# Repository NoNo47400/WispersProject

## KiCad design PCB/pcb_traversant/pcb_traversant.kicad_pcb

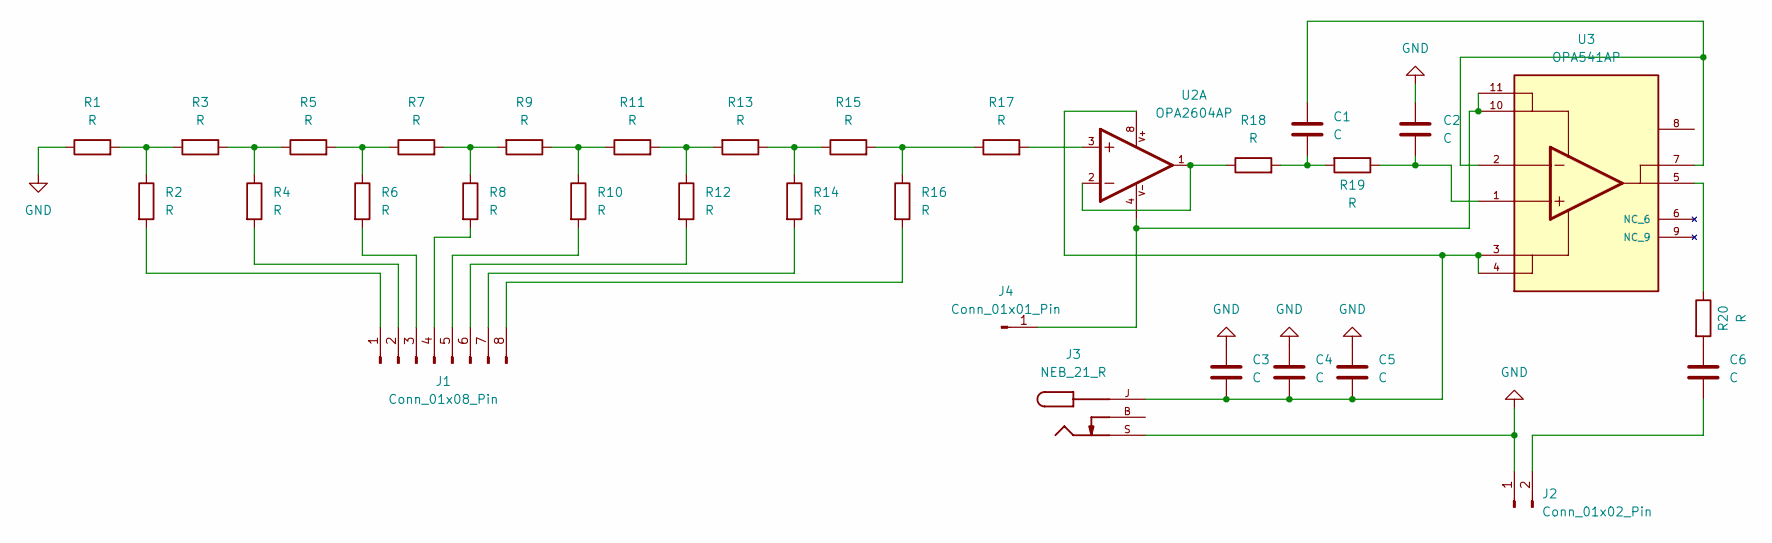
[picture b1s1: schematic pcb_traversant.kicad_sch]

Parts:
C1, C2, C3, C4, C5, C6: C; C_Rect_L4.0mm_W2.5mm_P2.50mm
J1: Conn_01x08_Pin; PinSocket_1x08_P2.54mm_Vertical
J2: Conn_01x02_Pin; PinHeader_1x02_P2.54mm_Vertical
J3: NEB_21_R; LUMBERG_NEB_21_R; PARTREV 01/2018
J4: Conn_01x01_Pin; PinHeader_1x01_P2.54mm_Horizontal
R1, R2, R3, R4, R5, R6, R7, R8, R9, R10, R11, R12, R13, R14, R15, R16, R17, R18, R19, R20: R; R_Bare_Metal_Element_L12.4mm_W4.8mm_P11.40mm
U2: OPA2604AP; DIP794W45P254L1016H508Q8; PARTREV A
U3: OPA541AP; TO170P2027X462X2456-11; PARTREV B

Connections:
GND: C2.1, C3.1, C4.1, C5.1, J2.1, J3.S, R1.1
unnamed: C1.1, U3.2, U3.7
unnamed: C1.2, R18.2, R19.2
unnamed: C2.2, R19.1, U3.1
unnamed: C3.2, C4.2, C5.2, J3.J, U2.8, U3.3, U3.4
unnamed: C6.1, R20.2
unnamed: J1.1, R2.2
unnamed: J1.2, R4.2
unnamed: J1.3, R6.2
unnamed: J1.4, R8.2
unnamed: J1.5, R10.2
unnamed: J1.6, R12.2
unnamed: J1.7, R14.2
unnamed: J1.8, R16.2
unnamed: C6.2, J2.2
unnamed: J4.1, U2.4, U3.10, U3.11
unnamed: R1.2, R2.1, R3.2
unnamed: R3.1, R4.1, R5.1
unnamed: R5.2, R6.1, R7.1
unnamed: R7.2, R8.1, R9.2
unnamed: R9.1, R10.1, R11.1
unnamed: R11.2, R12.1, R13.2
unnamed: R13.1, R14.1, R15.1
unnamed: R15.2, R16.1, R17.1
unnamed: R17.2, U2.3
unnamed: R18.1, U2.1, U2.2
unnamed: R20.1, U3.5

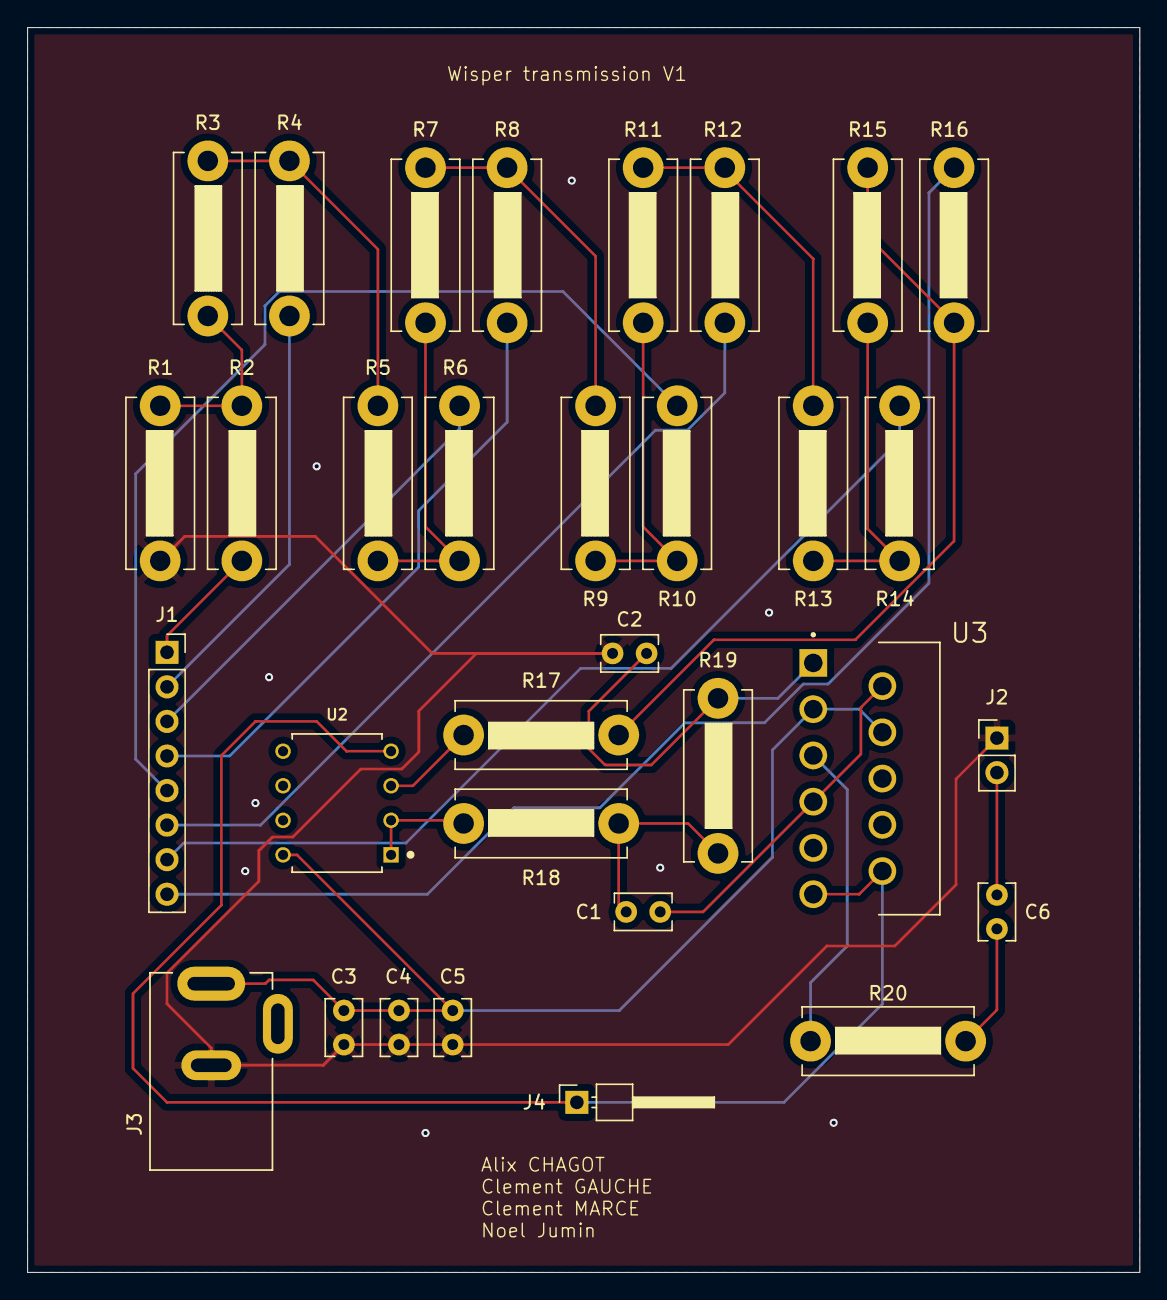
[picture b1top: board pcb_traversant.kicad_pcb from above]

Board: 2 copper layers, 81.8 x 91.5 mm, 32 parts (0 on the bottom side), 27 nets.

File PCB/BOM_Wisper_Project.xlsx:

| Label | Valeur / Composant | Nombre | Commentaire | Stock | Code Mouser
Transmission | R1 | 20k | 1
 | R2 | 20k | 1
 | R3 | 10k | 1
 | R4 | 20k | 1
 | R5 | 10k | 1
 | R6 | 20k | 1
 | R7 | 10k | 1
 | R8 | 20k | 1
 | R9 | 10k | 1
 | R10 | 20k | 1
 | R11 | 10k | 1
 | R12 | 20k | 1
 | R13 | 10k | 1
 | R14 | 20k | 1 |  |  |  | Les 2 BOMs en x2
 | R15 | 10k | 1
 | R16 | 20k | 1
 | R17 | 156k | 1
 | R18 | 1k | 1
 | R19 | 1k | 1
 | R20 | 9 | 1 | Adapter en fonction de la bobine émettrice
 | C1 | 100p | 1
 | C2 | 100p | 1
 | C3 | 1u | 1
 | C4 | 100n | 1
 | C5 | 10n | 1
 | C6 | 91p | 1 | Adapter en fonction de la bobine émettrice
 | J1 | Connecteur 8 broches | 1
 | J2 | Connecteur 2 broches | 1
 | J3 | Connecteur alimentation standard | 1 |  |  | 490-PJ-035DH
 | J4 | Connecteur 1 broche | 1
 | U2A | OPA2604AP | 1
 | U3 | OPA541AP | 1 |  |  | 595-OPA541AP
Réception | R1 | 9 | 1 | Adapter en fonction de la bobine émettrice
 | R2 | 1k | 1
 | R3 | 1k | 1
 | C1 | 1u | 1
 | C2 | 100n | 1
 | C3 | 10n | 1
 | C4 | 91p | 1 | Adapter en fonction de la bobine émettrice
 | C5 | 100n | 1
 | C6 | 100n | 1
 | J1 | Connecteur 2 broches | 1
 | J2 | Connecteur 2 broches | 1
 | J3 | Connecteur alimentation standard | 1 |  |  | 490-PJ-035DH
 | U1 | OPA541AP | 1 |  |  | 595-OPA541AP

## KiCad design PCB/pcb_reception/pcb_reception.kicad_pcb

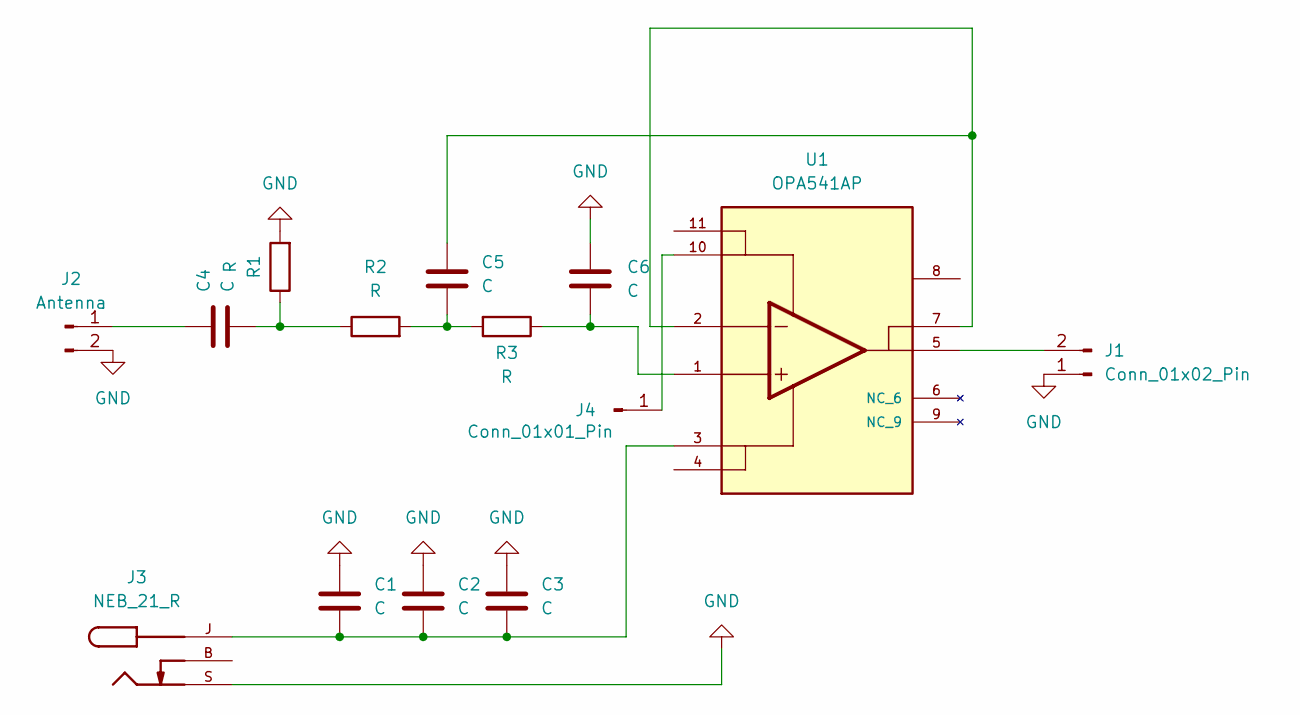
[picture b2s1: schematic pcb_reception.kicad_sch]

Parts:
C1, C2, C3, C4, C5, C6: C; C_Rect_L4.0mm_W2.5mm_P2.50mm
J1: Conn_01x02_Pin; PinHeader_1x02_P2.54mm_Vertical
J2: Antenna; PinHeader_1x02_P2.54mm_Vertical
J3: NEB_21_R; LUMBERG_NEB_21_R; PARTREV 01/2018
J4: Conn_01x01_Pin; PinHeader_1x01_P2.54mm_Horizontal
R1, R2, R3: R; R_Bare_Metal_Element_L12.4mm_W4.8mm_P11.40mm
U1: OPA541AP; TO170P2027X462X2456-11; PARTREV B

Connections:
GND: C1.1, C2.1, C3.1, C6.1, J1.1, J2.2, J3.S, R1.2
unnamed: C1.2, C2.2, C3.2, J3.J, U1.3
unnamed: C4.2, R1.1, R2.1
unnamed: C5.1, U1.2, U1.7
unnamed: C5.2, R2.2, R3.2
unnamed: C6.2, R3.1, U1.1
unnamed: J1.2, U1.5
unnamed: C4.1, J2.1
unnamed: J4.1, U1.10

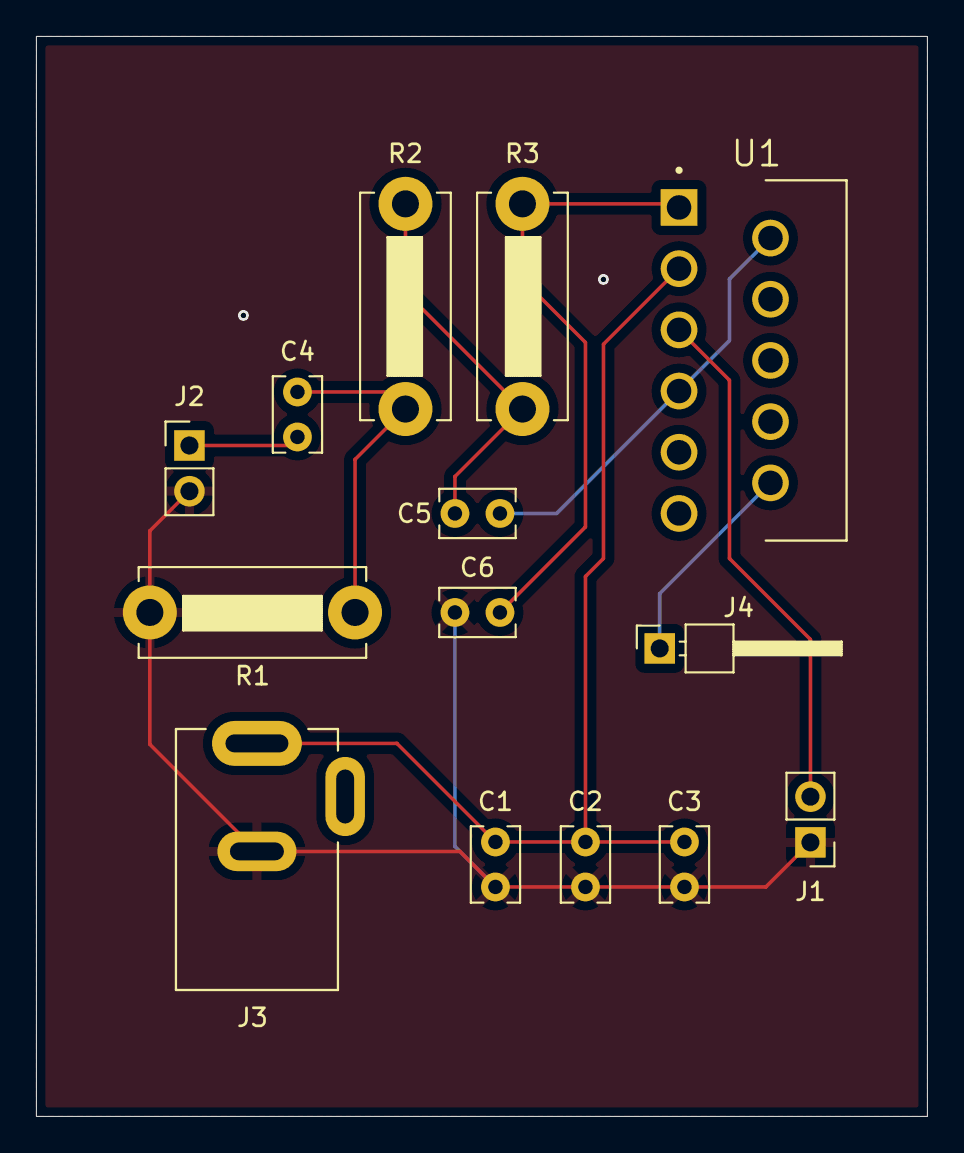
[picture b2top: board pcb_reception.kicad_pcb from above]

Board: 2 copper layers, 49.5 x 60.0 mm, 14 parts (0 on the bottom side), 9 nets.

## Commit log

2024-11-20 Ajout readme
2024-11-20 Creation platformio esp8266 avec mqtt qui écoute correctement
2024-11-20 Création d'un fichier pour gérer connexion wifi
2024-11-20 ajout nouveau truc pour mqtt, à continuer
2024-11-23 Test de la reception sur raspberry et store
2024-11-23 Reception qui fonctionne
2024-11-23 test de si ça fonctionne toute la chaine de communication avec la gateway
2024-11-24 la comm mqtt marche correctement et respecte la MAE définit, il faut revoir un peu le cpp en ajoutant peut etre un thread qui lit les messages mqtt car là il va soit trop vite et demande trop de fois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
2024-11-24 Masterclass de ma part, tout fonctionne parfaitement, envoi de trop de requeste corrigé aussi
2024-11-26 Décomposition en plusieurs fichiers
2024-12-04 Add FCS calculation and fuzzing scripts
    - Implement `calculate_fcs` function in `fcs.py` to compute Frame Check Sequence (FCS) for a given list of nibbles.
    - Add `fcs_fuzzing.py` script to perform fuzzing on FCS calculation by changing one bit at a time and checking for conflicts.
    - Add `fcs_fuzzing2.py` script to find collisions in FCS calculation by testing different combinations of nibble data.
2024-12-04 Add `calculate_fcs.vhd` for Rubee Protocol VHDL implementation
    - Implement `calculate_fcs` function in VHDL for computing Frame Check Sequence (FCS) as part of the Rubee Protocol.
2024-12-04 Replace `calculate_fcs` with `nibble_crc` for CRC computation
    - Add `nibble_crc.vhd` to compute CRC on nibbles (4 bits) instead of bytes.
    - Add `nibble_crc_sim.vhd` for simulating and verifying the nibble-based CRC computation.
2024-12-04 Add `create_request_pdu.vhd` and `create_request_pdu_sim.vhd` for PDU creation
    - Implement `create_request_pdu.vhd` to handle the creation of request PDUs (Protocol Data Units).
    - Add `create_request_pdu_sim.vhd` for simulating and verifying the PDU creation process.
2024-12-04 Add `RuBee.vhd` and `RuBee_sim.vhd` for Rubee Protocol
    - Implement `RuBee.vhd` to interface and use `create_request_pdu` for PDU creation.
    - Add `RuBee_sim.vhd` for simulating and verifying the functionality of the `RuBee` module.
2024-12-04 Update VHDL file descriptions and remove calculate_fcs.vhd and its simulation
    - Update header descriptions for `RuBee.vhd`, `RuBee_sim.vhd`, `create_request_pdu.vhd`, `create_request_pdu_sim.vhd`, `nibble_crc.vhd`, and `nibble_crc_sim.vhd`.
    - Remove `calculate_fcs.vhd` and its simulation file as they are replaced by `nibble_crc.vhd`.
2024-12-05 added to project
2024-12-05 Ajout des simulations de la transmission (filtre + amplificateur RF, ajout de la simulation du réseau R2R (DAC), ajout des simulations de réception, ajout des PCB de transmission et réception V1
2024-12-05 Ajout plan de masse et via sur les 2 PCB
2024-12-08 Ajout de la BOM des pcb de réception et d'émission
2024-12-15 Code qui compile, à tester
2024-12-16 Rubee qui fonctionne enfin avec le retour i2c simulé, code à améliorer et tester avec vrai i2c
2024-12-17 Finished BMC encoder and decoder with testbenches and simulation files
2024-12-17 ajout du front end qui affiche un dashboard avec les capteurs, en fonction de l'utilisateur connecté, fonctionne avec une base de donnée pour les utilisateurs, des templates de pages web et les donné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
2024-12-18 Updated and renamed create_request_pdu to create_pdu.
    - create_pdu can now also create response pdu.
    - Update RuBee.vhd to create_pdu interface.
    - Correction of the size of the protocol_selector
2024-12-19 Ajout modulation et debut de la demodulation
2024-12-24 Modification des 2 composants BMC afin qu'ils soient synthétisables et implémentable, les simulations sont fonctionnelles ainsi que sur le FPGA
2025-01-02 Commit initial pour cette branche
2025-01-02 Ajout de l'adresse ip sur laquelle déployer l'application
2025-01-02 Modification de l'interface
2025-01-02 Placement de la database qui n'était pas au bon endroit pour que les deux programmes y accedent
2025-01-02 Modification du path de la database dans les codes qui y font appel
2025-01-02 Modification du mqtt_server.py car messages séparés par ; et non ,
2025-01-02 Fautes d'orthographe dans l'appel des colonnes de la database
2025-01-02 Modification de la table pour pouvoir voir les patchs de chaque hub
2025-01-02 Correction de l'app
2025-01-02 Changement de l'appel à la base sql
2025-01-02 Ce n'était pas le bon id qui était utilisé pour chacune des tables
2025-01-02 Ajout affichage en temps réel des données
2025-01-12 ajout de la renitialisation de la base de donnée au démarrage pour les capteurs et hubs
2025-01-12 Ajout de data i2c simulé pour avoir de plus beaux graphes
2025-01-16 Mise a jour du calcul et de l'intégration du FCS. Création des composants header_detection & decode_pdu.
2025-01-26 Detection en-tete en reception
2025-01-26 Retrait des integer dans les ports
2025-01-26 modu et demodu simu logique OK
2025-01-27 create_pdu fonctionnel et implémentable decode_pdu buggé
2025-01-29 design et opti clock
2025-01-29 Renommage decode_pdu
2025-02-12 Final version BMC
